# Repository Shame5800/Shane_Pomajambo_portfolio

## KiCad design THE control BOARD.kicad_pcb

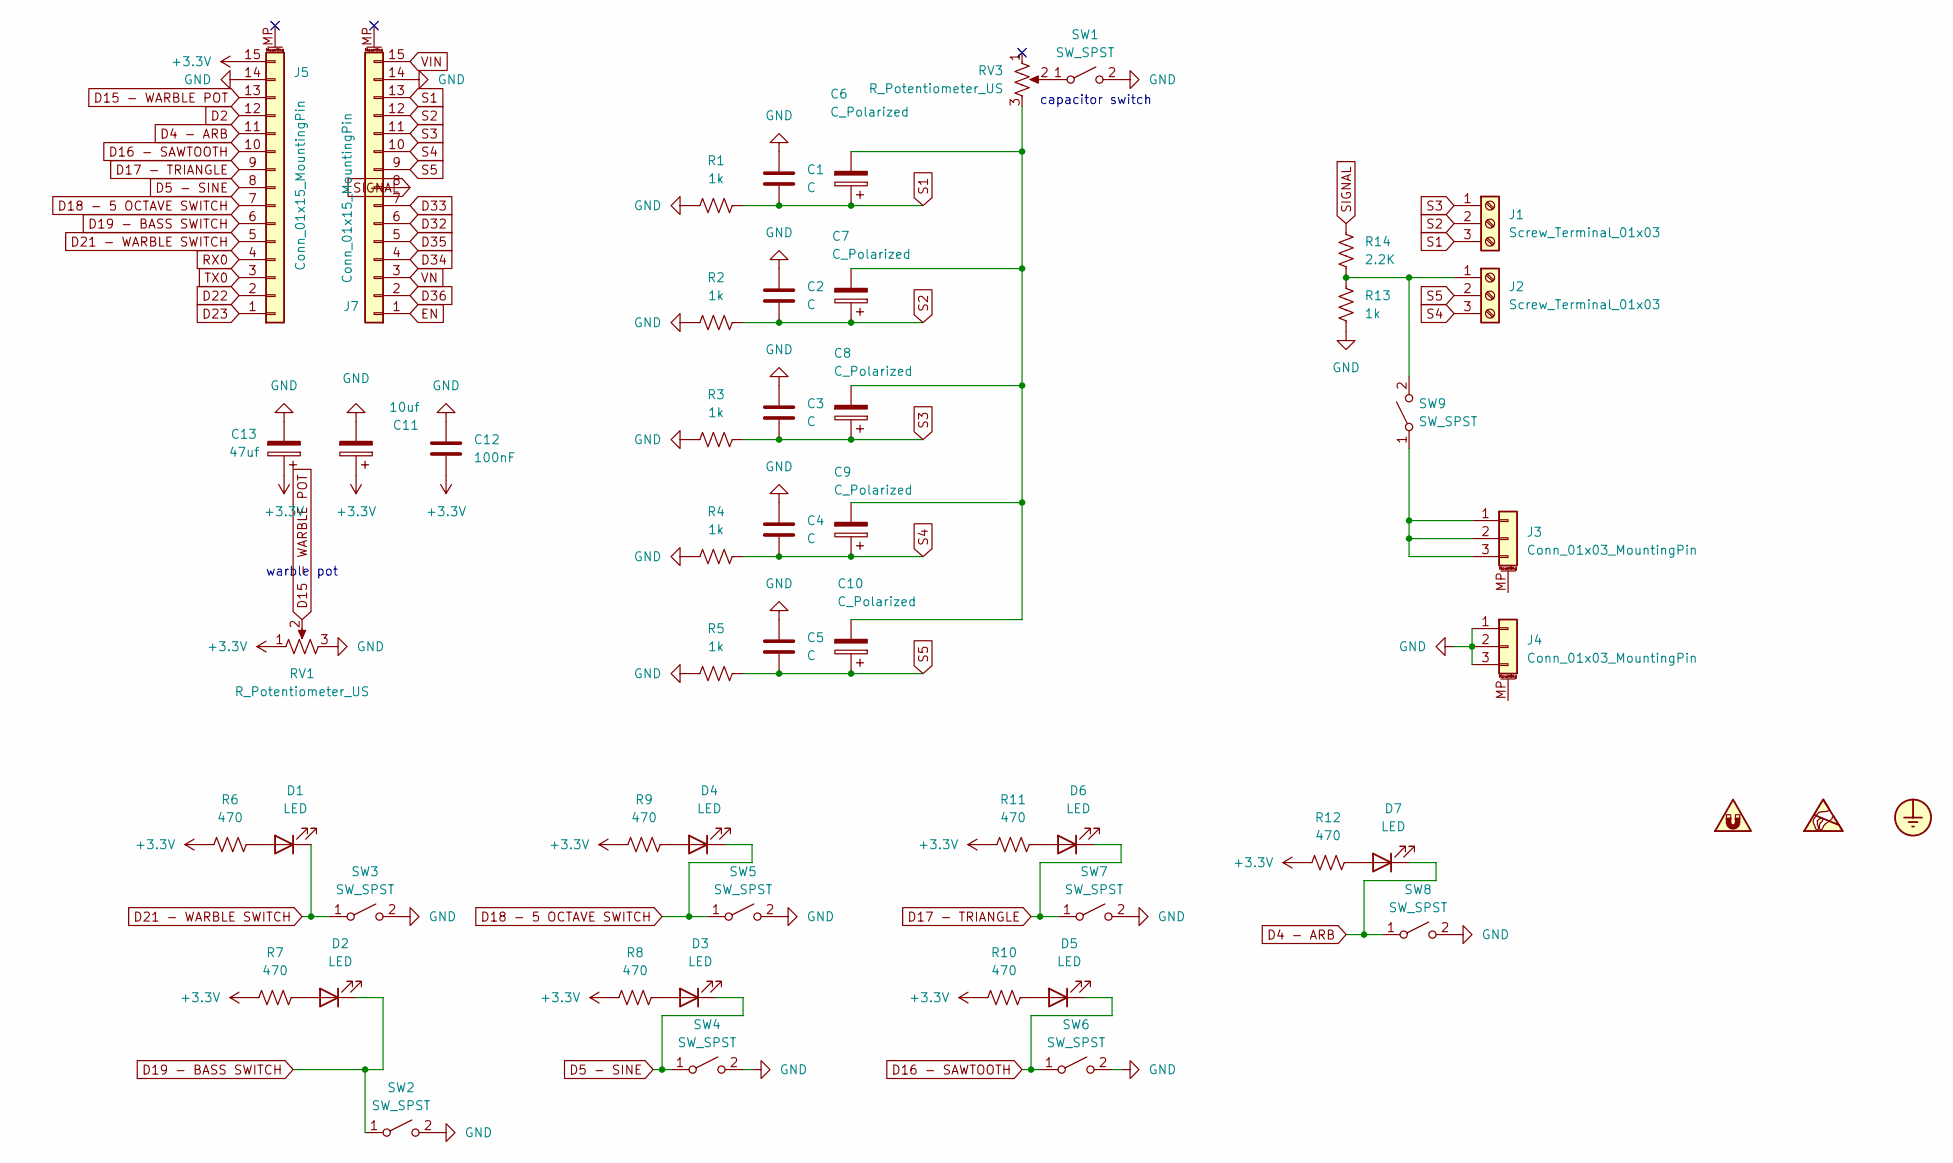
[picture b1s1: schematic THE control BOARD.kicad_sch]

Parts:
C1, C2, C3, C4, C5: C; C_Rect_L10.0mm_W2.5mm_P7.50mm_MKS4
C6, C7, C8, C9, C10: C_Polarized; CP_Radial_D4.0mm_P2.00mm
C11: 10uf; CP_Radial_D4.0mm_P2.00mm
C12: 100nF; CP_Radial_Tantal_D9.0mm_P5.00mm
C13: 47uf; CP_Radial_D4.0mm_P2.00mm
D1, D2, D3, D4, D5, D6, D7: LED; LED_D3.0mm
J1, J2: Screw_Terminal_01x03; TerminalBlock_MetzConnect_Type011_RT05503HBLC_1x03_P5.00mm_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
J3, J4: Conn_01x03_MountingPin; PinSocket_1x03_P2.54mm_Vertical
J5, J7: Conn_01x15_MountingPin; PinSocket_1x15_P2.54mm_Vertical
R1, R2, R3, R4, R5, R13: 1k; R_Axial_DIN0207_L6.3mm_D2.5mm_P10.16mm_Horizontal
R6, R7, R8, R9, R10, R11, R12: 470; R_Axial_DIN0207_L6.3mm_D2.5mm_P10.16mm_Horizontal
R14: 2.2K; R_Axial_DIN0207_L6.3mm_D2.5mm_P10.16mm_Horizontal
RV1, RV3: R_Potentiometer_US; potentiometer
SW1, SW2, SW3, SW4, SW5, SW6, SW7, SW8, SW9: SW_SPST; Untitled

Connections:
+3.3V: C11.1, C12.2, C13.1, J5.15, R6.1, R7.1, R8.1, R9.1, R10.1, R11.1, R12.1, RV1.1
D2: J5.12
D4 - ARB: D7.1 (K), J5.11, SW8.1 (A)
D5 - SINE: D3.1 (K), J5.8, SW4.1 (A)
D15 - WARBLE POT: J5.13, RV1.2
D16 - SAWTOOTH: D5.1 (K), J5.10, SW6.1 (A)
D17 - TRIANGLE: D6.1 (K), J5.9, SW7.1 (A)
D18 - 5 OCTAVE SWITCH: D4.1 (K), J5.7, SW5.1 (A)
D19 - BASS SWITCH: D2.1 (K), J5.6, SW2.1 (A)
D21 - WARBLE SWITCH: D1.1 (K), J5.5, SW3.1 (A)
D22: J5.2
D23: J5.1
D32: J7.6
D33: J7.7
D34: J7.4
D35: J7.5
D36: J7.2
EN: J7.1
GND: C1.1, C2.1, C3.1, C4.1, C5.1, C11.2, C12.1, C13.2, J4.1, J4.2, J4.3, J5.14, J7.14, R1.1, R2.1, R3.1, R4.1, R5.1, R13.1, RV1.3, SW1.2 (B), SW2.2 (B), SW3.2 (B), SW4.2 (B), SW5.2 (B), SW6.2 (B), SW7.2 (B), SW8.2 (B)
unnamed: C6.2, C7.2, C8.2, C9.2, C10.2, RV3.3
unnamed: D1.2 (A), R6.2
unnamed: D2.2 (A), R7.2
unnamed: D3.2 (A), R8.2
unnamed: D4.2 (A), R9.2
unnamed: D5.2 (A), R10.2
unnamed: D6.2 (A), R11.2
unnamed: D7.2 (A), R12.2
unnamed: J2.1, R13.2, R14.1, SW9.2 (B)
unnamed: J3.1, J3.2, J3.3, SW9.1 (A)
unnamed: RV3.2, SW1.1 (A)
RX0: J5.4
S1: C1.2, C6.1, J1.3, J7.13, R1.2
S2: C2.2, C7.1, J1.2, J7.12, R2.2
S3: C3.2, C8.1, J1.1, J7.11, R3.2
S4: C4.2, C9.1, J2.3, J7.10, R4.2
S5: C5.2, C10.1, J2.2, J7.9, R5.2
SIGNAL: J7.8, R14.2
TX0: J5.3
VIN: J7.15
VN: J7.3

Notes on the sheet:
capacitor switch
warble pot

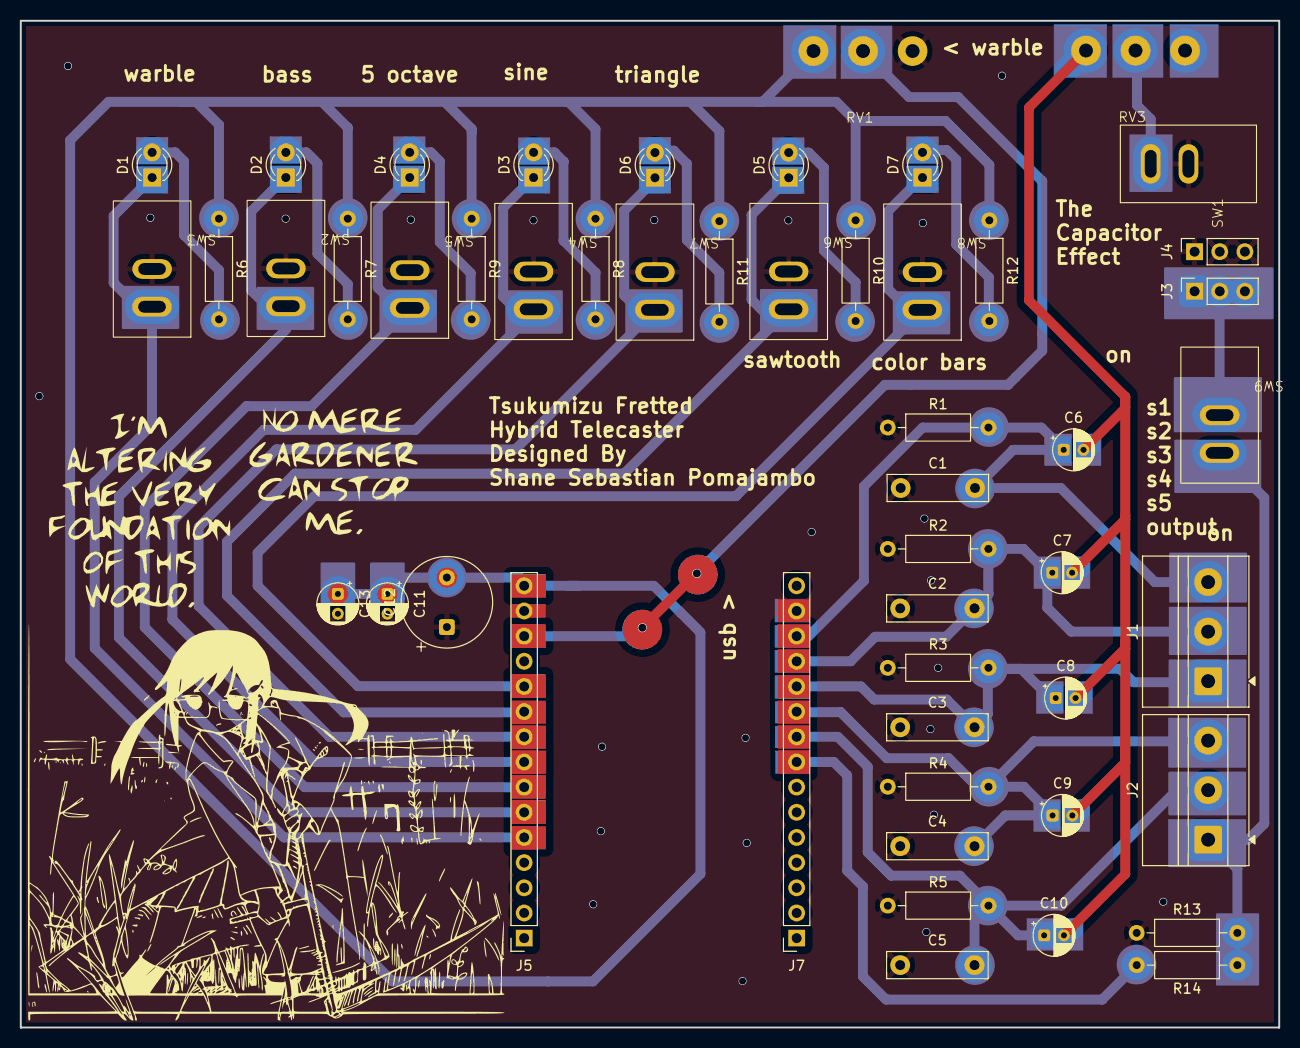
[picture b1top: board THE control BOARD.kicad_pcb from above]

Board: 2 copper layers, 127.0 x 101.6 mm, 51 parts (0 on the bottom side), 27 nets.

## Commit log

2026-04-28 Barebones website
